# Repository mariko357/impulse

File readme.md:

# Impulse
***
## Todo:
- [ ] Create a propper readme, I guess.

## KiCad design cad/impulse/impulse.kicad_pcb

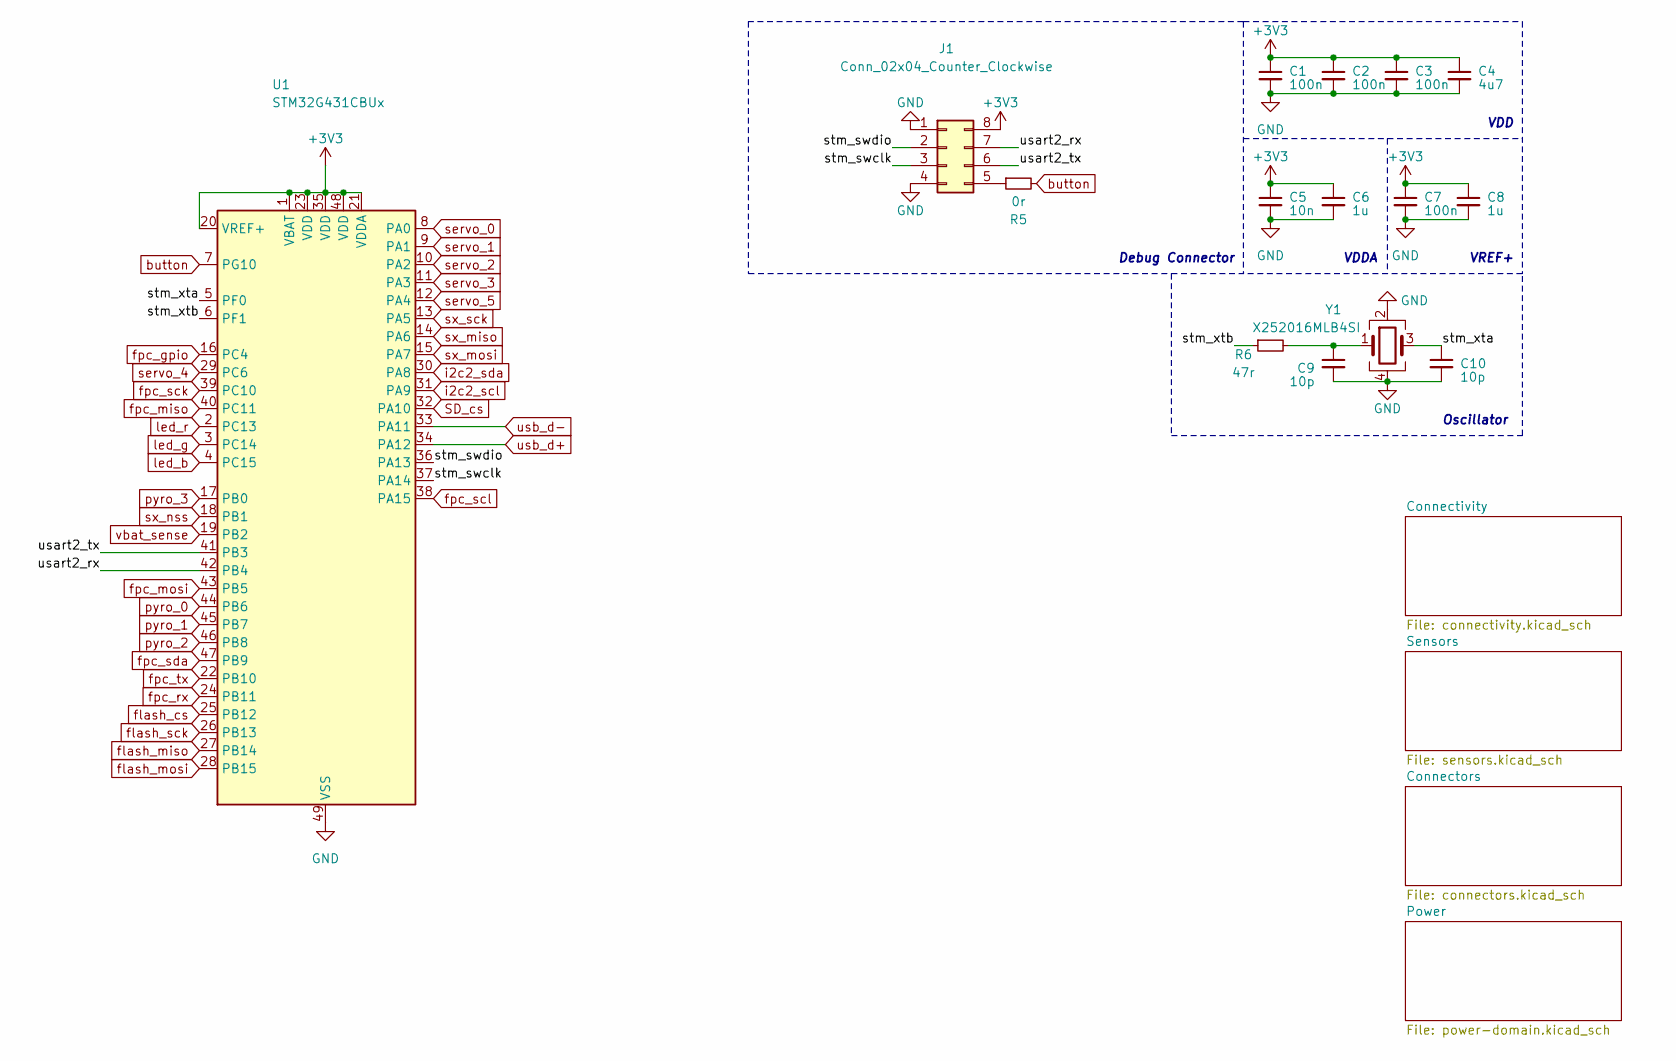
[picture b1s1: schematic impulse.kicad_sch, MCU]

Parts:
C1, C2, C3, C7: 100n; C_0402_1005Metric; lcsc C1525
C4: 4u7; C_0603_1608Metric; lcsc C5360855
C5: 10n; C_0603_1608Metric; lcsc C525264
C6, C8: 1u; C_0603_1608Metric; lcsc C167338
C9, C10: 10p; C_0402_1005Metric; lcsc C1545
J1: Conn_02x04_Counter_Clockwise; PinHeader_2x04_P1.27mm_Vertical_SMD; lcsc C2685182
R5: 0r; R_0402_1005Metric; lcsc C21376
R6: 47r; R_0402_1005Metric; lcsc C2906947
U1: STM32G431CBUx; QFN-48-1EP_7x7mm_P0.5mm_EP5.6x5.6mm; lcsc C529356
Y1: X252016MLB4SI; Crystal_SMD_2520-4Pin_2.5x2.0mm; lcsc C784073

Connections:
+3V3: C1.1, C2.1, C3.1, C4.1, C5.1, C6.1, C7.1, C8.1, J1.8, U1.1 (VBAT), U1.20 (VREF+), U1.21 (VDDA), U1.23 (VDD), U1.35 (VDD), U1.48 (VDD); also elsewhere on the board
/stm_swclk: J1.3, U1.37 (PA14)
/stm_swdio: J1.2, U1.36 (PA13)
/stm_xta: C10.1, U1.5 (PF0), Y1.3
/stm_xtb: R6.1, U1.6 (PF1)
/usart2_rx: J1.7, U1.42 (PB4)
/usart2_tx: J1.6, U1.41 (PB3)
GND: C1.2, C2.2, C3.2, C4.2, C5.2, C6.2, C7.2, C8.2, C9.2, C10.2, J1.1, J1.4, U1.49 (VSS), Y1.2, Y1.4; also elsewhere on the board
unnamed: C9.1, R6.2, Y1.1
unnamed: J1.5, R5.1
SD_cs: U1.32 (PA10); also elsewhere on the board
button: R5.2, U1.7 (PG10); also elsewhere on the board
flash_cs: U1.25 (PB12); also elsewhere on the board
flash_miso: U1.27 (PB14); also elsewhere on the board
flash_mosi: U1.28 (PB15); also elsewhere on the board
flash_sck: U1.26 (PB13); also elsewhere on the board
fpc_gpio: U1.16 (PC4); also elsewhere on the board
fpc_miso: U1.40 (PC11); also elsewhere on the board
fpc_mosi: U1.43 (PB5); also elsewhere on the board
fpc_rx: U1.24 (PB11); also elsewhere on the board
fpc_sck: U1.39 (PC10); also elsewhere on the board
fpc_tx: U1.22 (PB10); also elsewhere on the board
led_b: U1.4 (PC15); also elsewhere on the board
led_g: U1.3 (PC14); also elsewhere on the board
led_r: U1.2 (PC13); also elsewhere on the board
pyro_0: U1.44 (PB6); also elsewhere on the board
pyro_1: U1.45 (PB7); also elsewhere on the board
pyro_2: U1.46 (PB8); also elsewhere on the board
pyro_3: U1.17 (PB0); also elsewhere on the board
servo_0: U1.8 (PA0); also elsewhere on the board
servo_1: U1.9 (PA1); also elsewhere on the board
servo_2: U1.10 (PA2); also elsewhere on the board
servo_3: U1.11 (PA3); also elsewhere on the board
servo_4: U1.29 (PC6); also elsewhere on the board
servo_5: U1.12 (PA4); also elsewhere on the board
sx_miso: U1.14 (PA6); also elsewhere on the board
sx_mosi: U1.15 (PA7); also elsewhere on the board
sx_nss: U1.18 (PB1); also elsewhere on the board
sx_sck: U1.13 (PA5); also elsewhere on the board
usb_d+: U1.34 (PA12); also elsewhere on the board
usb_d-: U1.33 (PA11); also elsewhere on the board
vbat_sense: U1.19 (PB2); also elsewhere on the board

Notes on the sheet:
VREF+
VDD
Oscillator
Debug Connector
VDDA

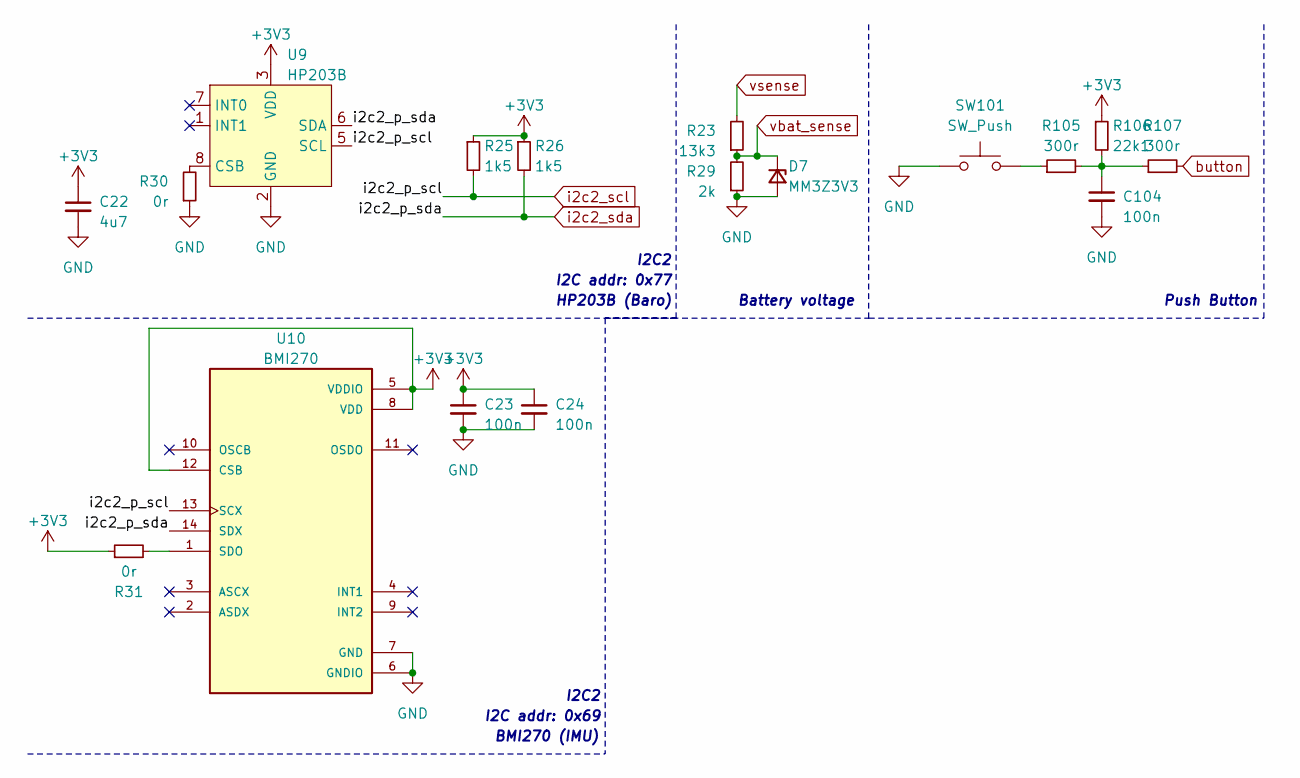
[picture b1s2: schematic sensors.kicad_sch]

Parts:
C22: 4u7; C_0603_1608Metric; lcsc C5360855
C23, C24, C104: 100n; C_0402_1005Metric; lcsc C1525
D7: MM3Z3V3; D_SOD-323; lcsc C2978809
R23: 13k3; R_0402_1005Metric; lcsc C3015832
R25, R26: 1k5; R_0402_1005Metric; lcsc C3017483
R29: 2k; R_0402_1005Metric; lcsc C3152076
R30, R31: 0r; R_0402_1005Metric; lcsc C21376
R105, R107: 300r; R_0402_1005Metric; lcsc C3017471
R106: 22k1; R_0402_1005Metric; lcsc C5356129
SW101: SW_Push; GT-TC029B-H025-L1N; lcsc C843669
U9: HP203B; QFN-8-P09; lcsc C138665
U10: BMI270; LGA-14_3x2.5mm_P0.5mm_LayoutBorder3x4y; lcsc C2836813

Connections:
+3V3: C22.1, C23.1, C24.1, R25.1, R26.1, R31.1, U9.3 (VDD), U10.5 (VDDIO), U10.8 (VDD), U10.12 (CSB); also elsewhere on the board
GND: C22.2, C23.2, C24.2, D7.2 (A), R29.1, R30.1, U9.2 (GND), U10.6 (GNDIO), U10.7 (GND); also elsewhere on the board
unnamed: R30.2, U9.8 (CSB)
unnamed: R31.2, U10.1 (SDO)
vbat_sense: D7.1 (K), R23.1, R29.2; also elsewhere on the board
vsense: R23.2; also elsewhere on the board

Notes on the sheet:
BMI270 (IMU)
I2C2
I2C addr: 0x69
HP203B (Baro)
Push Button
Battery voltage
I2C addr: 0x77

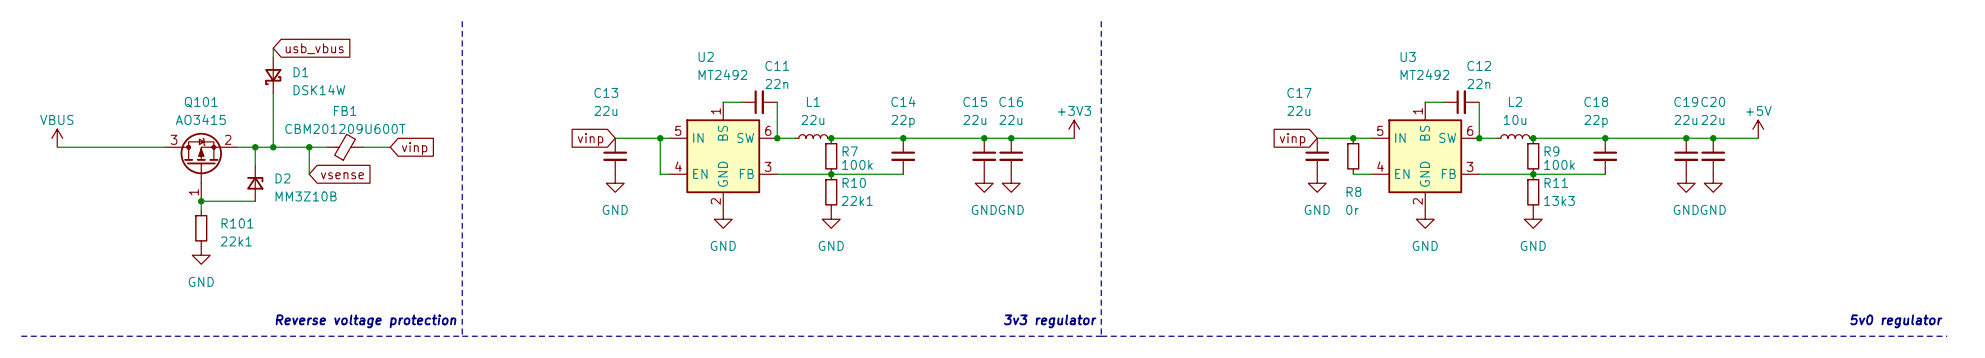
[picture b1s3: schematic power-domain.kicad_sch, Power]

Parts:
C11, C12: 22n; C_0402_1005Metric; lcsc C5137627
C13, C15, C16, C17, C19, C20: 22u; C_1206_3216Metric; lcsc C2858005
C14, C18: 22p; C_0402_1005Metric; lcsc C5137569
D1: DSK14W; D_SOD-123F; lcsc C3014043
D2: MM3Z10B; D_SOD-323; lcsc C2826565
FB1: CBM201209U600T; R_0805_2012Metric; lcsc C139167
L1: 22u; L_1210_3225Metric; lcsc C223225
L2: 10u; L_Sunlord_MWSA0402S; lcsc C2921170
Q101: AO3415; SOT-23; lcsc C181094
R7, R9: 100k; R_0402_1005Metric; lcsc C3017514
R8: 0r; R_0402_1005Metric; lcsc C21376
R10, R101: 22k1; R_0402_1005Metric; lcsc C5356129
R11: 13k3; R_0402_1005Metric; lcsc C3015832
U2, U3: MT2492; SOT-23-6; lcsc C89358

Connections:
+3V3: C14.1, C15.1, C16.1, L1.2, R7.1; also elsewhere on the board
+5V: C18.1, C19.1, C20.1, L2.2, R9.1; also elsewhere on the board
GND: C13.2, C15.2, C16.2, C17.2, C19.2, C20.2, R10.2, R11.2, U2.2 (GND), U3.2 (GND); also elsewhere on the board
unnamed 24: D2.2 (A); also elsewhere on the board
unnamed: C11.1, U2.1 (BS)
unnamed: C14.2, R7.2, R10.1, U2.3 (FB)
unnamed: C11.2, L1.1, U2.6 (SW)
unnamed: C12.1, U3.1 (BS)
unnamed: R8.2, U3.4 (EN)
unnamed: C18.2, R9.2, R11.1, U3.3 (FB)
unnamed: C12.2, L2.1, U3.6 (SW)
usb_vbus: D1.2 (A); also elsewhere on the board
vinp: C13.1, C17.1, FB1.2, R8.1, U2.4 (EN), U2.5 (IN), U3.5 (IN); also elsewhere on the board
vsense: D1.1 (K), D2.1 (K), FB1.1; also elsewhere on the board

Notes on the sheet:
5v0 regulator
3v3 regulator
Reverse voltage protection

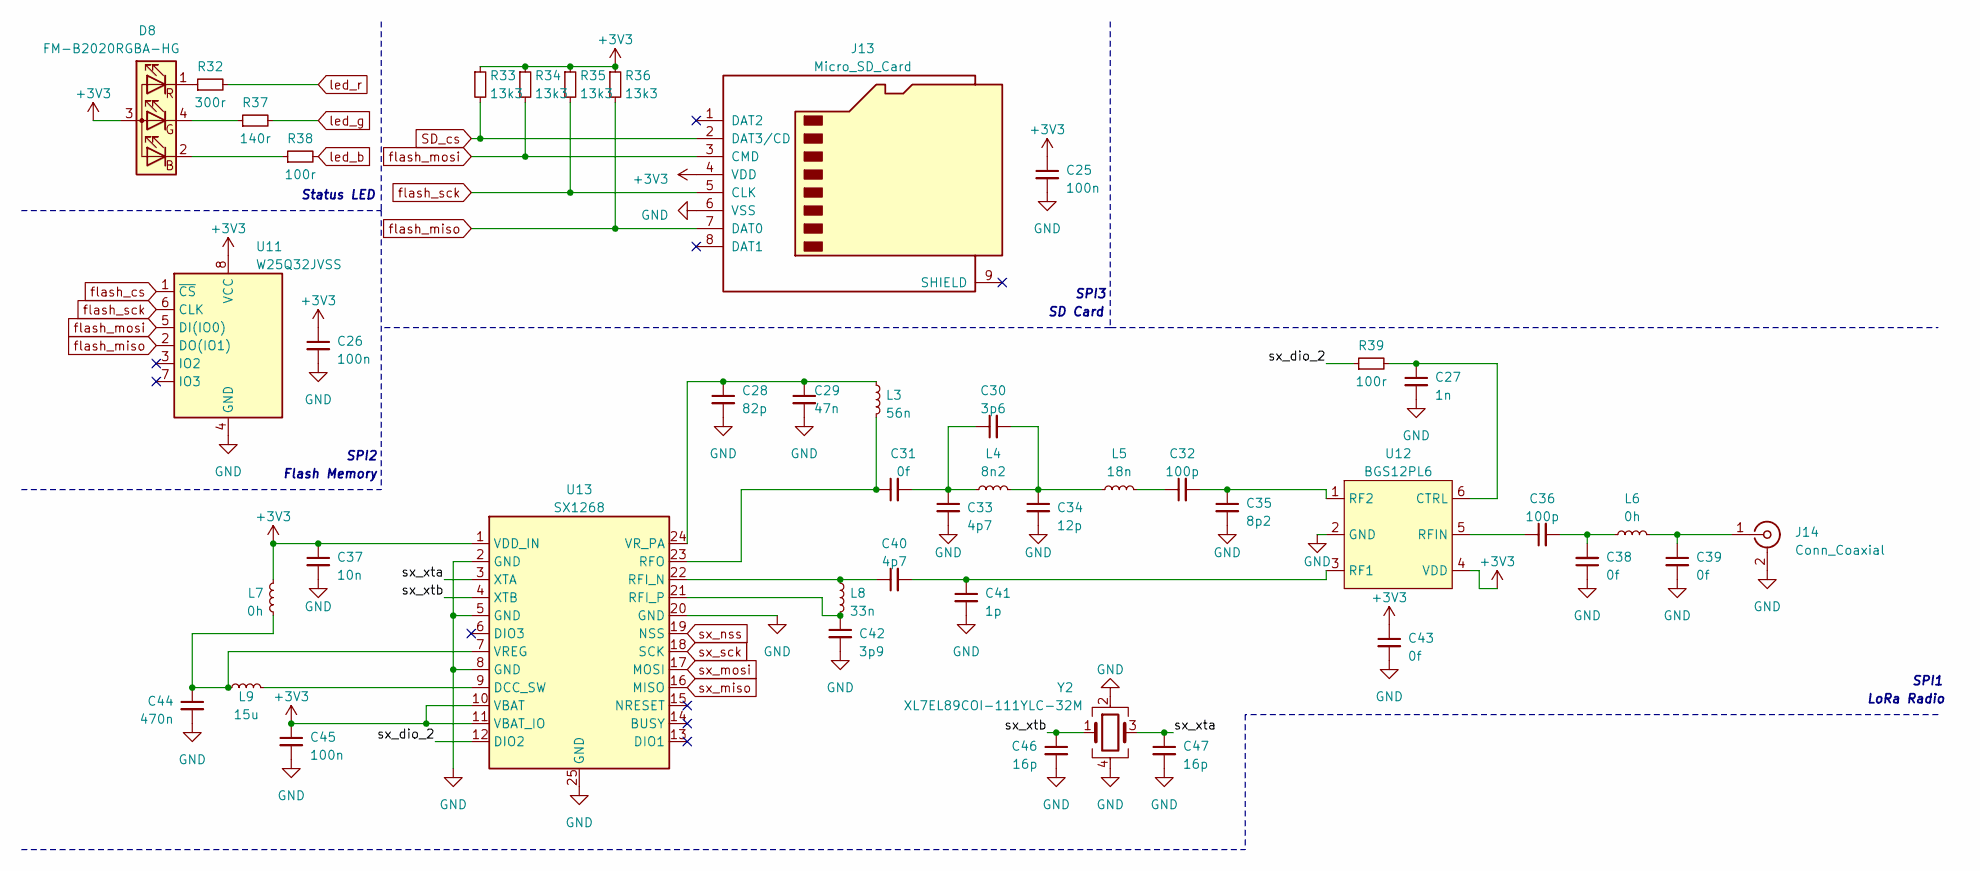
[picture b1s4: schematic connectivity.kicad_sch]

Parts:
C25, C26, C45: 100n; C_0402_1005Metric; lcsc C1525
C27: 1n; C_0201_0603Metric; lcsc C301889
C28: 82p; C_0201_0603Metric; lcsc C285023
C29: 47n; C_0201_0603Metric; lcsc C513424
C30: 3p6; C_0201_0603Metric; lcsc C525056
C31, C38, C39, C43: 0f; C_0201_0603Metric; lcsc C3152011
C32, C36: 100p; C_0201_0603Metric; lcsc C5142539
C33, C40: 4p7; C_0201_0603Metric; lcsc C525057
C34: 12p; C_0201_0603Metric; lcsc C50391
C35: 8p2; C_0201_0603Metric; lcsc C913427
C37: 10n; C_0603_1608Metric; lcsc C525264
C41: 1p; C_0201_0603Metric; lcsc C285009
C42: 3p9; C_0201_0603Metric; lcsc C285000
C44: 470n; C_0402_1005Metric; lcsc C5142573
C46, C47: 16p; C_0402_1005Metric; lcsc C5142569
D8: FM-B2020RGBA-HG; lcsc C108793
J13: Micro_SD_Card; microSD-Generic; lcsc C393941
J14: Conn_Coaxial; U.FL_Hirose_U.FL-R-SMT-1_Vertical; lcsc C5299419
L3: 56n; L_0201_0603Metric; lcsc C963966
L4: 8n2; L_0201_0603Metric; lcsc C2941401
L5: 18n; L_0201_0603Metric; lcsc C2913989
L6: 0h; L_0201_0603Metric; lcsc C3152011
L7: 0h; L_0402_1005Metric; lcsc C21376
L8: 33n; L_0201_0603Metric; lcsc C211337
L9: 15u; L_0805_2012Metric; lcsc C383402
R32: 300r; R_0402_1005Metric; lcsc C3017471
R33, R34, R35, R36: 13k3; R_0402_1005Metric; lcsc C3015832
R37: 140r; R_0402_1005Metric; lcsc C3015963
R38, R39: 100r; R_0402_1005Metric; lcsc C3152058
U11: W25Q32JVSS; SOIC-8_5.23x5.23mm_P1.27mm; lcsc C2834491
U12: BGS12PL6; lcsc C2939943
U13: SX1268; QFN-24-1EP_4x4mm_P0.5mm_EP2.7x2.7mm; lcsc C244368
Y2: XL7EL89COI-111YLC-32M; Crystal_SMD_2016-4Pin_2.0x1.6mm; lcsc C2965584

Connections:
+3V3: C25.1, C26.1, C37.1, C43.1, C45.1, D8.3 (A), J13.4 (VDD), L7.1, R33.1, R34.1, R35.1, R36.1, U11.8 (VCC), U12.4 (VDD), U13.1 (VDD_IN), U13.10 (VBAT), U13.11 (VBAT_IO); also elsewhere on the board
/Connectivity/sx_dio_2: R39.1, U13.12 (DIO2)
/Connectivity/sx_xta: C47.1, U13.3 (XTA), Y2.3
/Connectivity/sx_xtb: C46.1, U13.4 (XTB), Y2.1
GND: C25.2, C26.2, C27.2, C28.2, C29.2, C33.2, C34.2, C35.2, C37.2, C38.1, C39.2, C41.2, C42.2, C43.2, C44.2, C45.2, C46.2, C47.2, J13.6 (VSS), J14.2 (Ext), U11.4 (GND), U12.2 (GND), U13.2 (GND), U13.5 (GND), U13.8 (GND), U13.20 (GND), U13.25 (GND), Y2.2, Y2.4; also elsewhere on the board
unnamed: C30.1, C31.2, C33.1, L4.1
unnamed: C30.2, C34.1, L4.2, L5.1
unnamed: C32.1, L5.2
unnamed: C36.2, C38.2, L6.1
unnamed: D8.2 (BK), R38.1
unnamed: D8.4 (GK), R37.1
unnamed: D8.1 (RK), R32.1
unnamed: C39.1, J14.1 (In), L6.2
unnamed: C27.1, R39.2, U12.6 (CTRL)
unnamed: C40.2, C41.1, U12.3 (RF1)
unnamed: C32.2, C35.1, U12.1 (RF2)
unnamed: C36.1, U12.5 (RFIN)
unnamed: L9.2, U13.9 (DCC_SW)
unnamed: C40.1, L8.1, U13.22 (RFI_N)
unnamed: C42.1, L8.2, U13.21 (RFI_P)
unnamed: C31.1, L3.2, U13.23 (RFO)
unnamed: C44.1, L7.2, L9.1, U13.7 (VREG)
unnamed: C28.1, C29.1, L3.1, U13.24 (VR_PA)
SD_cs: J13.2 (DAT3/CD), R33.2; also elsewhere on the board
flash_cs: U11.1 (~CS); also elsewhere on the board
flash_miso: J13.7 (DAT0), R36.2, U11.2 (DO(IO1)); also elsewhere on the board
flash_mosi: J13.3 (CMD), R34.2, U11.5 (DI(IO0)); also elsewhere on the board
flash_sck: J13.5 (CLK), R35.2, U11.6 (CLK); also elsewhere on the board
led_b: R38.2; also elsewhere on the board
led_g: R37.2; also elsewhere on the board
led_r: R32.2; also elsewhere on the board
sx_miso: U13.16 (MISO); also elsewhere on the board
sx_mosi: U13.17 (MOSI); also elsewhere on the board
sx_nss: U13.19 (NSS); also elsewhere on the board
sx_sck: U13.18 (SCK); also elsewhere on the board

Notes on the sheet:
SPI2
SPI3
LoRa Radio
Status LED
SPI1
Flash Memory
SD Card

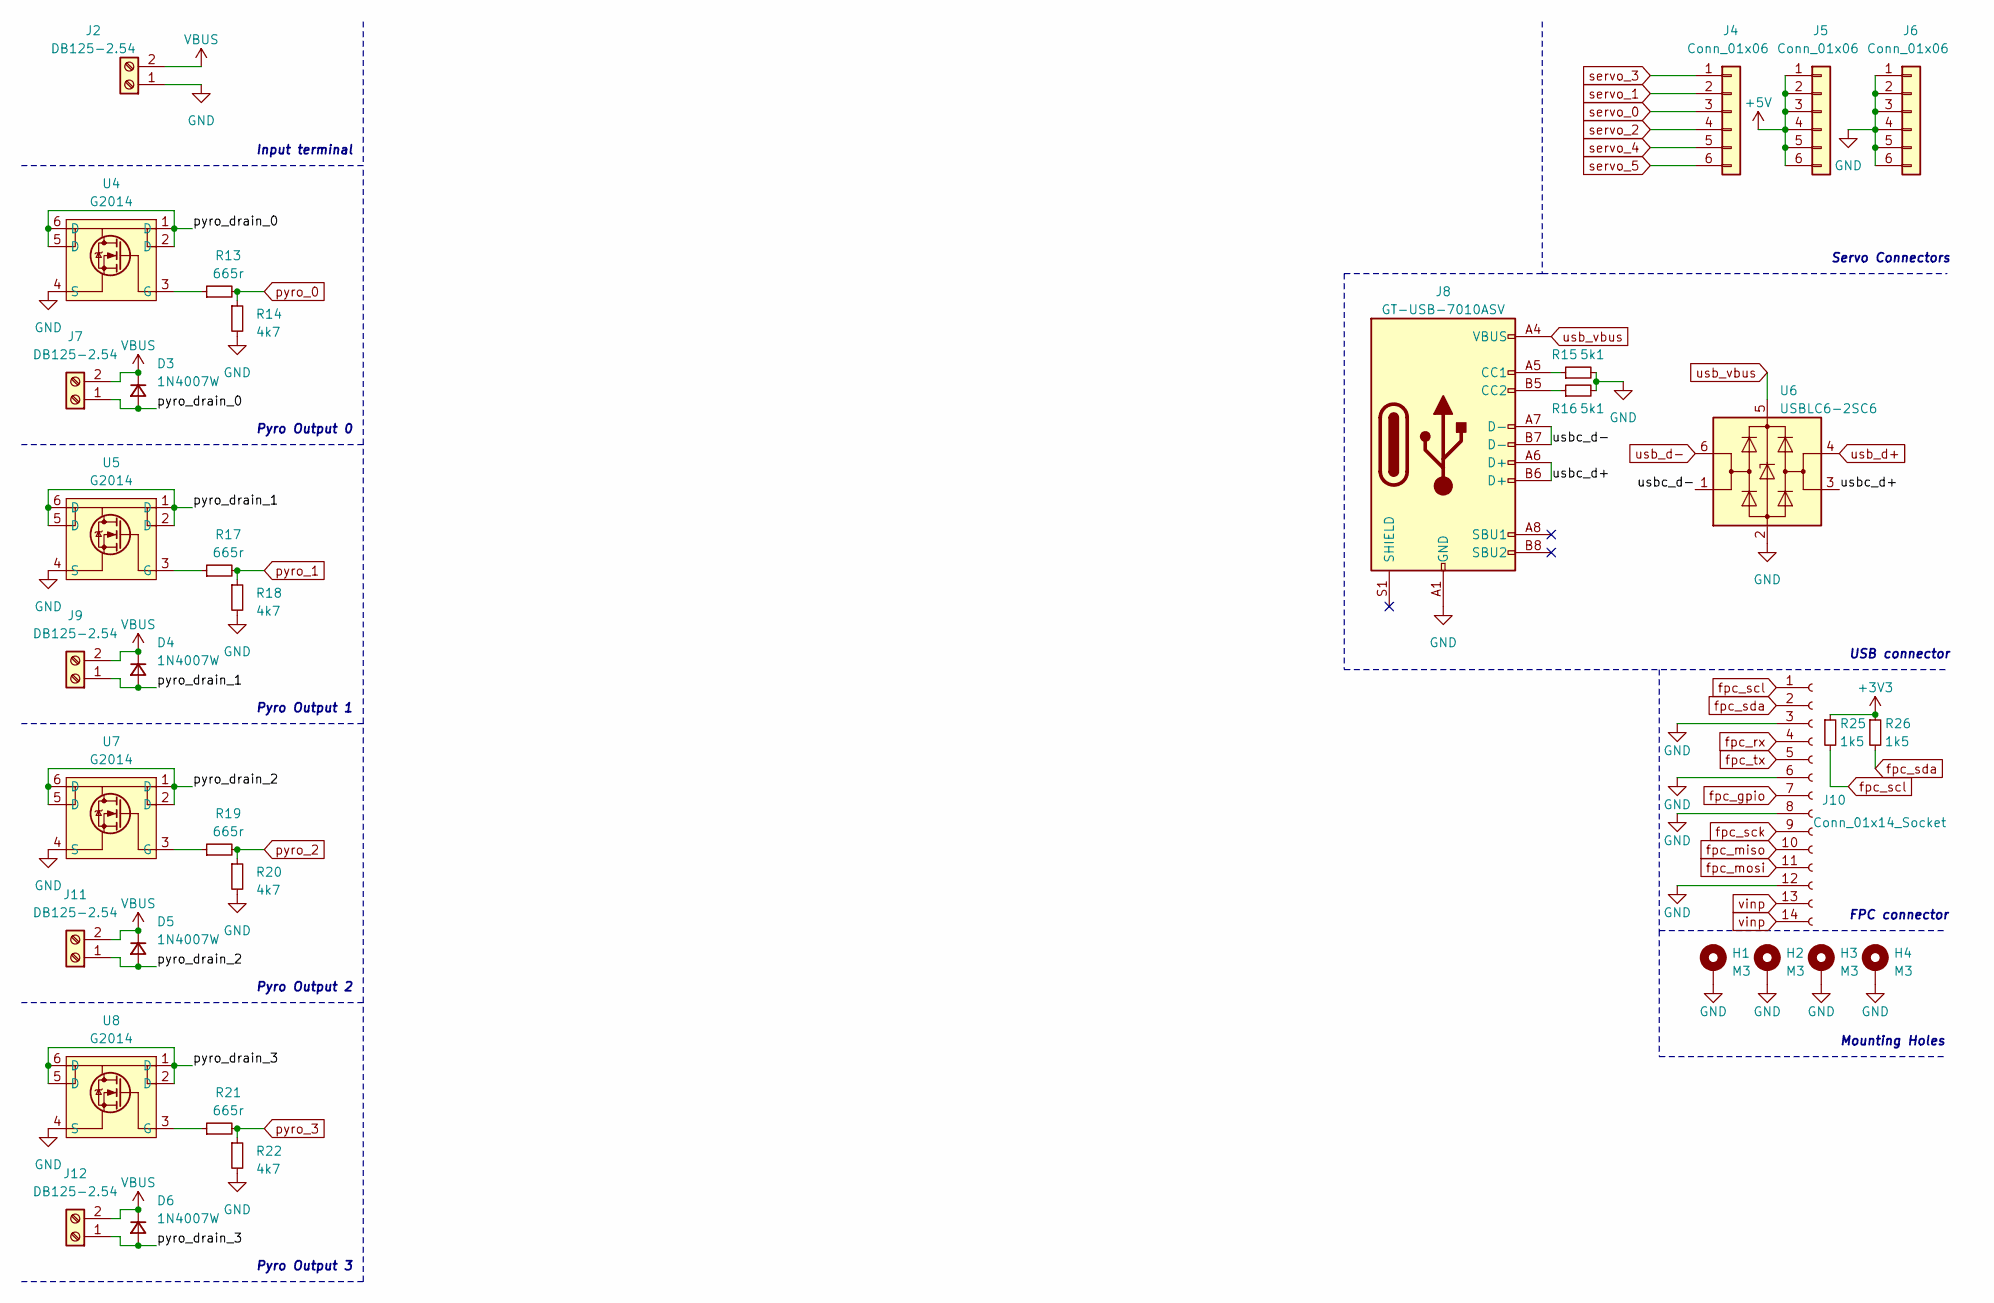
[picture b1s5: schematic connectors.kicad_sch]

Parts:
D3, D4, D5, D6: 1N4007W; D_SOD-123F; lcsc C727082
H1, H2, H3, H4: M3; MountingHole_3.2mm_M3_Pad_Via
J2: DB125-2.54; TerminalBlock_TE_282834-2_1x02_P2.54mm_Horizontal; lcsc C918120
J4, J5, J6: Conn_01x06; PinHeader_1x06_P2.54mm_Vertical
J7, J9, J11, J12: DB125-2.54; TerminalBlock_TE_282834-2_1x02_P2.54mm_Horizontal; lcsc C918126
J8: GT-USB-7010ASV; USB_C_Receptacle_G-Switch_GT-USB-7010ASV; lcsc C2988369
J10: Conn_01x14_Socket; Hirose_FH12-14S-0.5SH_1x14-1MP_P0.50mm_Horizontal; lcsc C2856800
R13, R17, R19, R21: 665r; R_0402_1005Metric; lcsc C3015970
R14, R18, R20, R22: 4k7; R_0402_1005Metric; lcsc C103059
R15, R16: 5k1; R_0402_1005Metric; lcsc C3152095
R25, R26: 1k5; R_0402_1005Metric; lcsc C3017483
U4, U5, U7, U8: G2014; DFN-6-L; lcsc C3038579
U6: USBLC6-2SC6; SOT-23-6; lcsc C558442

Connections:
+3V3: R25.1, R26.1; also elsewhere on the board
+5V: J5.1, J5.2, J5.3, J5.4, J5.5, J5.6; also elsewhere on the board
/Connectors/pyro_drain_0: D3.2 (A), J7.1, U4.1 (D), U4.2 (D), U4.5 (D), U4.6 (D)
/Connectors/pyro_drain_1: D4.2 (A), J9.1, U5.1 (D), U5.2 (D), U5.5 (D), U5.6 (D)
/Connectors/pyro_drain_2: D5.2 (A), J11.1, U7.1 (D), U7.2 (D), U7.5 (D), U7.6 (D)
/Connectors/pyro_drain_3: D6.2 (A), J12.1, U8.1 (D), U8.2 (D), U8.5 (D), U8.6 (D)
/Connectors/usbc_d+: J8.A6 (D+), J8.B6 (D+), U6.3 (I/O2)
/Connectors/usbc_d-: J8.A7 (D-), J8.B7 (D-), U6.1 (I/O1)
GND: H1.1, H2.1, H3.1, H4.1, J2.1, J6.1, J6.2, J6.3, J6.4, J6.5, J6.6, J8.A1 (GND), J8.A12 (GND), J8.B1 (GND), J8.B12 (GND), J10.3, J10.6, J10.8, J10.12, R14.2, R15.2, R16.2, R18.2, R20.2, R22.2, U4.4 (S), U5.4 (S), U6.2 (GND), U7.4 (S), U8.4 (S); also elsewhere on the board
unnamed: J8.A5 (CC1), R15.1
unnamed: J8.B5 (CC2), R16.1
unnamed: R13.1, U4.3 (G)
unnamed: R17.1, U5.3 (G)
unnamed: R19.1, U7.3 (G)
unnamed: R21.1, U8.3 (G)
VBUS: D3.1 (K), D4.1 (K), D5.1 (K), D6.1 (K), J2.2, J7.2, J9.2, J11.2, J12.2; also elsewhere on the board
fpc_gpio: J10.7; also elsewhere on the board
fpc_miso: J10.10; also elsewhere on the board
fpc_mosi: J10.11; also elsewhere on the board
fpc_rx: J10.4; also elsewhere on the board
fpc_sck: J10.9; also elsewhere on the board
fpc_tx: J10.5; also elsewhere on the board
pyro_0: R13.2, R14.1; also elsewhere on the board
pyro_1: R17.2, R18.1; also elsewhere on the board
pyro_2: R19.2, R20.1; also elsewhere on the board
pyro_3: R21.2, R22.1; also elsewhere on the board
servo_0: J4.3; also elsewhere on the board
servo_1: J4.2; also elsewhere on the board
servo_2: J4.4; also elsewhere on the board
servo_3: J4.1; also elsewhere on the board
servo_4: J4.5; also elsewhere on the board
servo_5: J4.6; also elsewhere on the board
usb_d+: U6.4 (I/O2); also elsewhere on the board
usb_d-: U6.6 (I/O1); also elsewhere on the board
usb_vbus: J8.A4 (VBUS), J8.A9 (VBUS), J8.B4 (VBUS), J8.B9 (VBUS), U6.5 (VBUS); also elsewhere on the board
vinp: J10.13, J10.14; also elsewhere on the board

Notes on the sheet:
Pyro Output 1
Pyro Output 0
FPC connector
Pyro Output 3
USB connector
Pyro Output 2
Mounting Holes
Input terminal
Servo Connectors

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
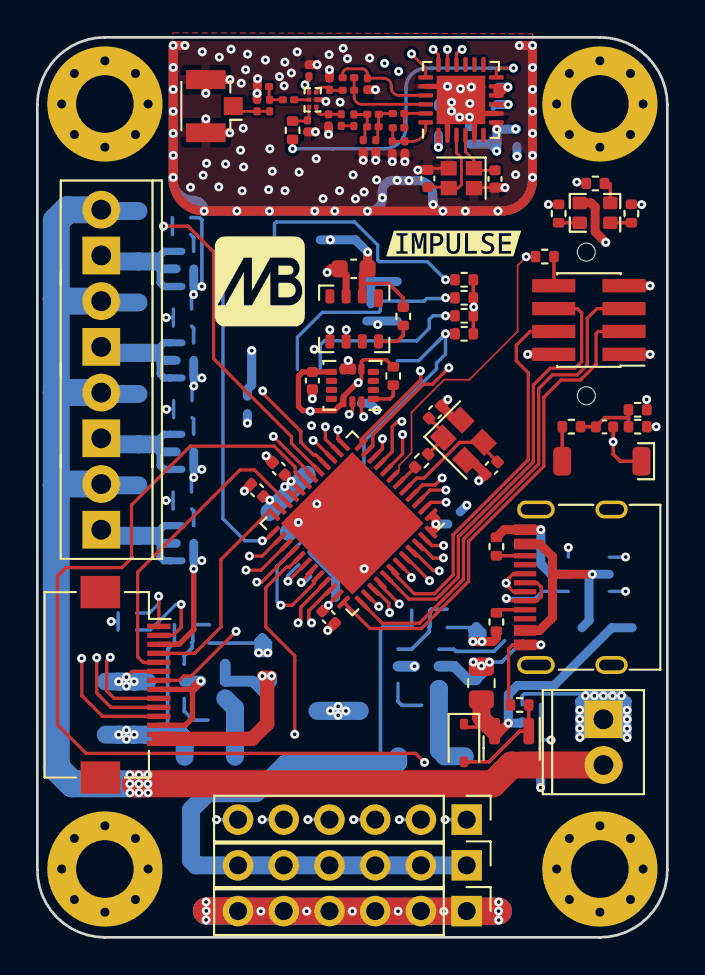
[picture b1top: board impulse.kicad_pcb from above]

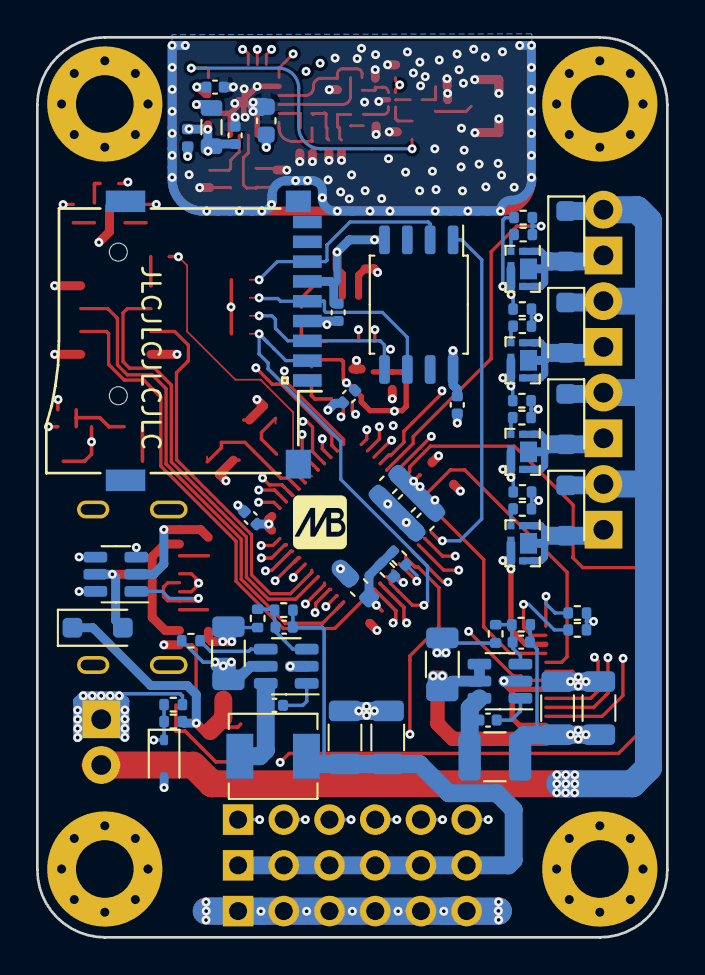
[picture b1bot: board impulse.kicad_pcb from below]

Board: 8 copper layers, 35.0 x 50.0 mm, 137 parts (59 on the bottom side), 96 nets.

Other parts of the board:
C21: 100n; C_0402_1005Metric
Q1: AO3415; SOT-23
R1, R2: 1k5; R_0402_1005Metric
R12, R24: 22k1; R_0402_1005Metric
R27, R28: 300r; R_0402_1005Metric
SW1: SW_Push; GT-TC029B-H025-L1N
kibuzzard-647A5142: G***; kibuzzard-647A5142

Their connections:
+3V3: R1.1, R2.1, R24.1; also elsewhere on the board
GND: C21.2, R12.2, SW1.1; also elsewhere on the board
unnamed: C21.1, R24.2, R27.2, R28.1
unnamed 24: Q1.1 (G), R12.1; also elsewhere on the board
unnamed: R27.1, SW1.2
VBUS: Q1.3 (D); also elsewhere on the board
button: R28.2; also elsewhere on the board
vsense: Q1.2 (S); also elsewhere on the board

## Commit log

2023-05-08 Added pyro channels and power domain.
2023-05-11 Changed the power domain to mt2492.
2023-05-11 Calculated smps values and modified .gitignore.
2023-05-12 Started Working on sensors. Made connectors for servos.
2023-05-13 Added IMU, button and led. Moved things around.
2023-05-13 Transitioned to global labels when needed.
2023-05-13 Added USB connector.
2023-05-16 Finished with LoRa.
2023-05-18 Finnished the design.
2023-05-19 Started working on BOM, did consolidation.
2023-05-21 Finished with schematic, starting to route traces.
2023-05-21 Modified oscillator circuit.
2023-05-27 First layout.
2023-07-16 Final version, ordered it.
2023-07-16 Ignoring bom folder now, added readme.
